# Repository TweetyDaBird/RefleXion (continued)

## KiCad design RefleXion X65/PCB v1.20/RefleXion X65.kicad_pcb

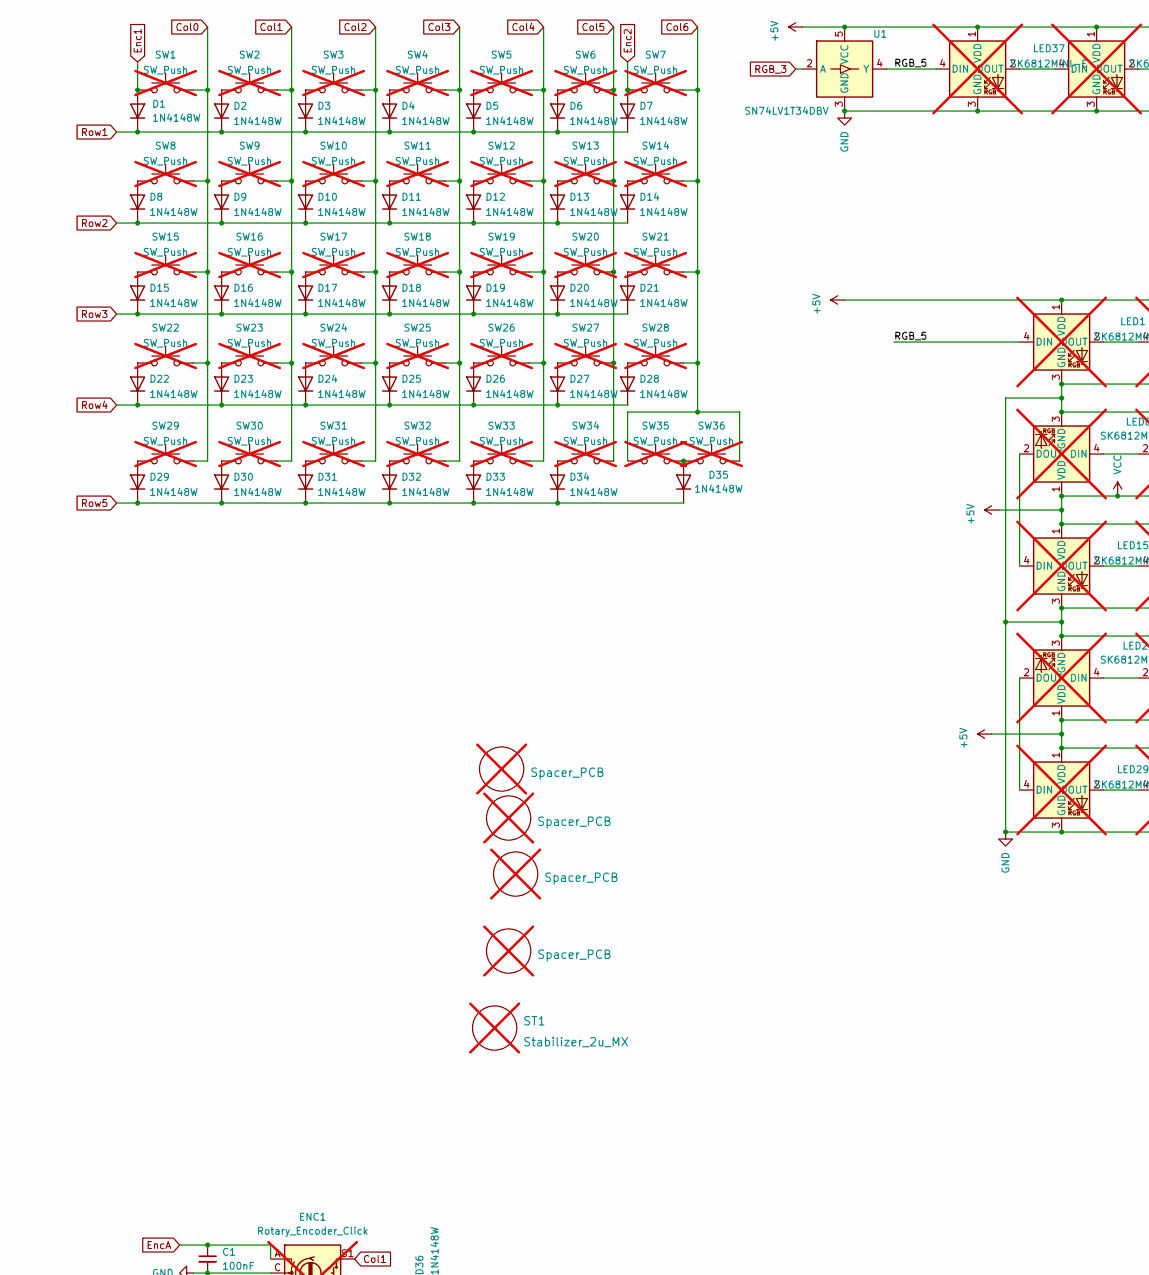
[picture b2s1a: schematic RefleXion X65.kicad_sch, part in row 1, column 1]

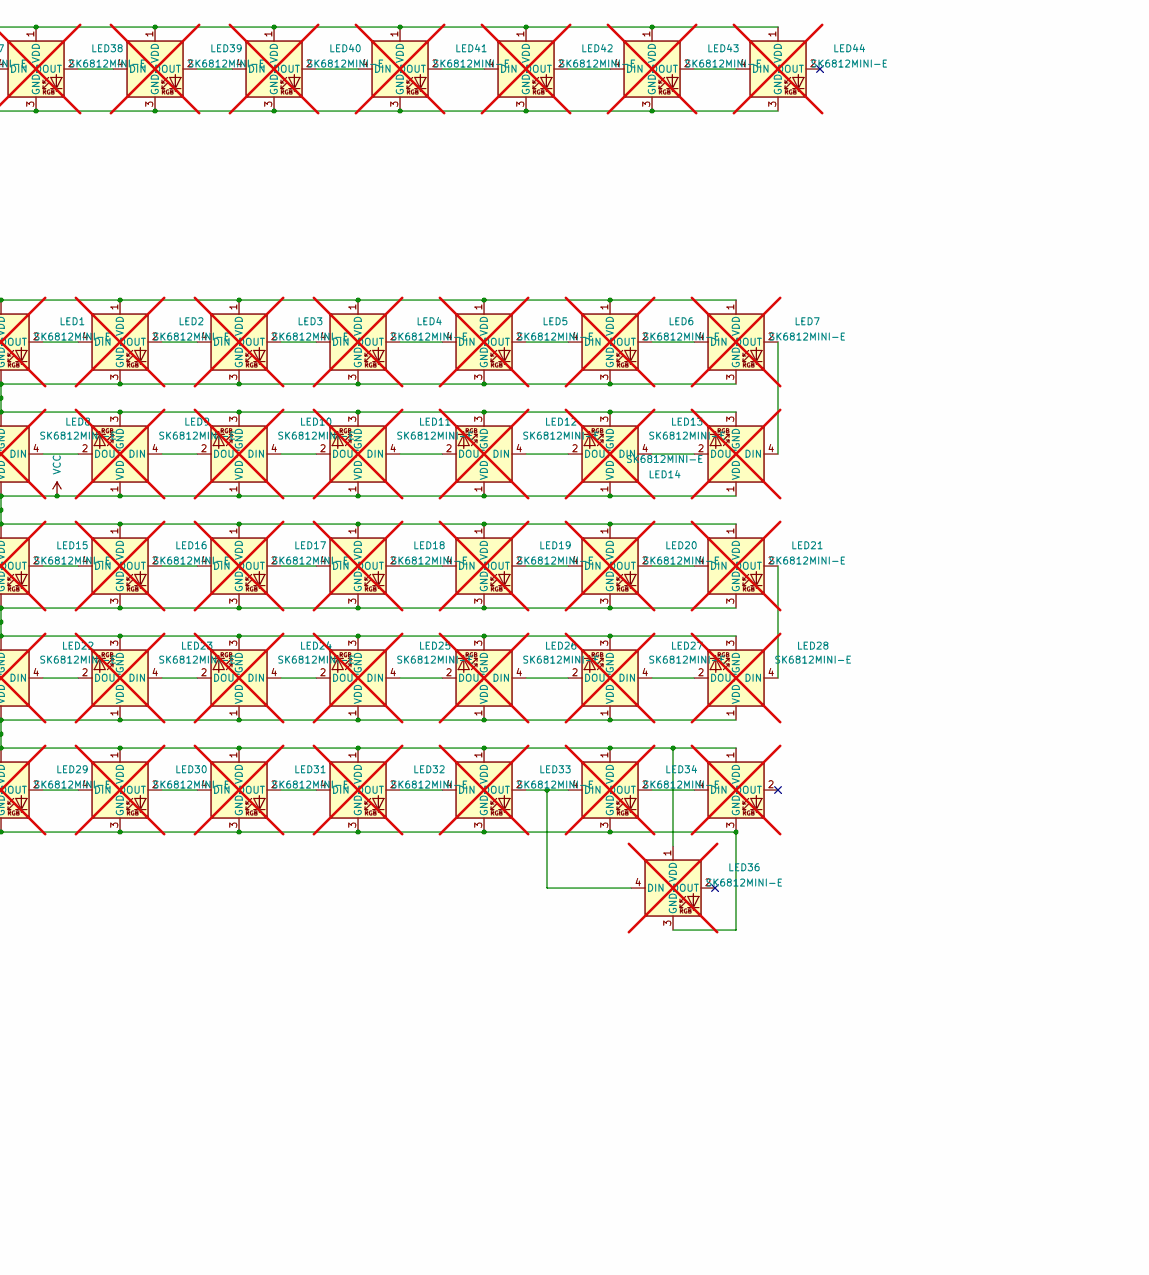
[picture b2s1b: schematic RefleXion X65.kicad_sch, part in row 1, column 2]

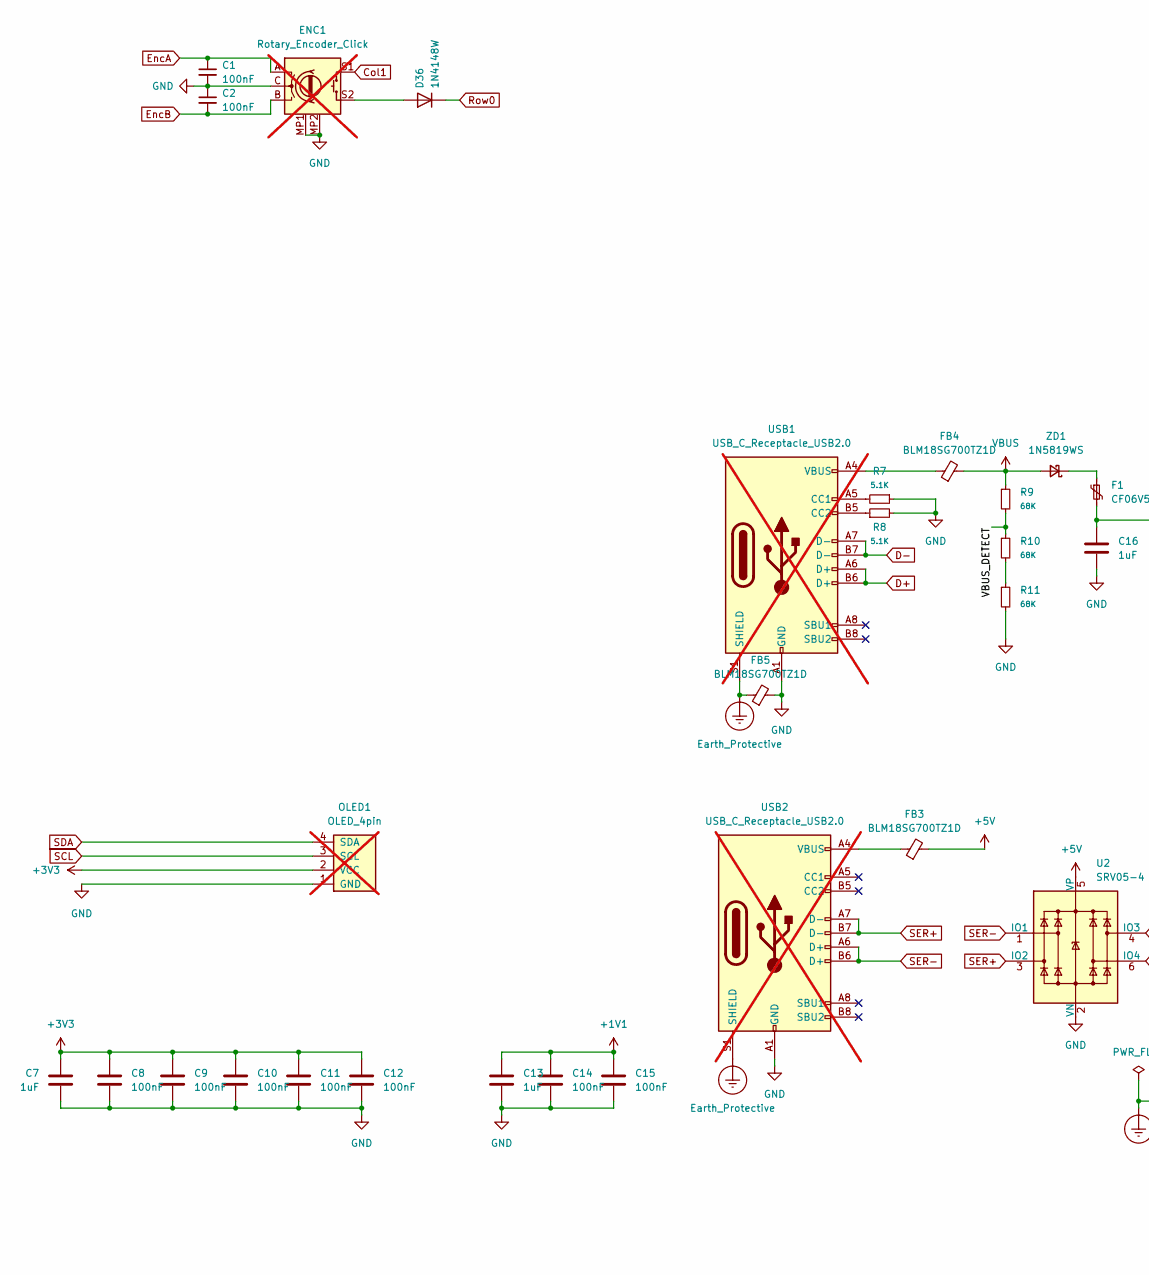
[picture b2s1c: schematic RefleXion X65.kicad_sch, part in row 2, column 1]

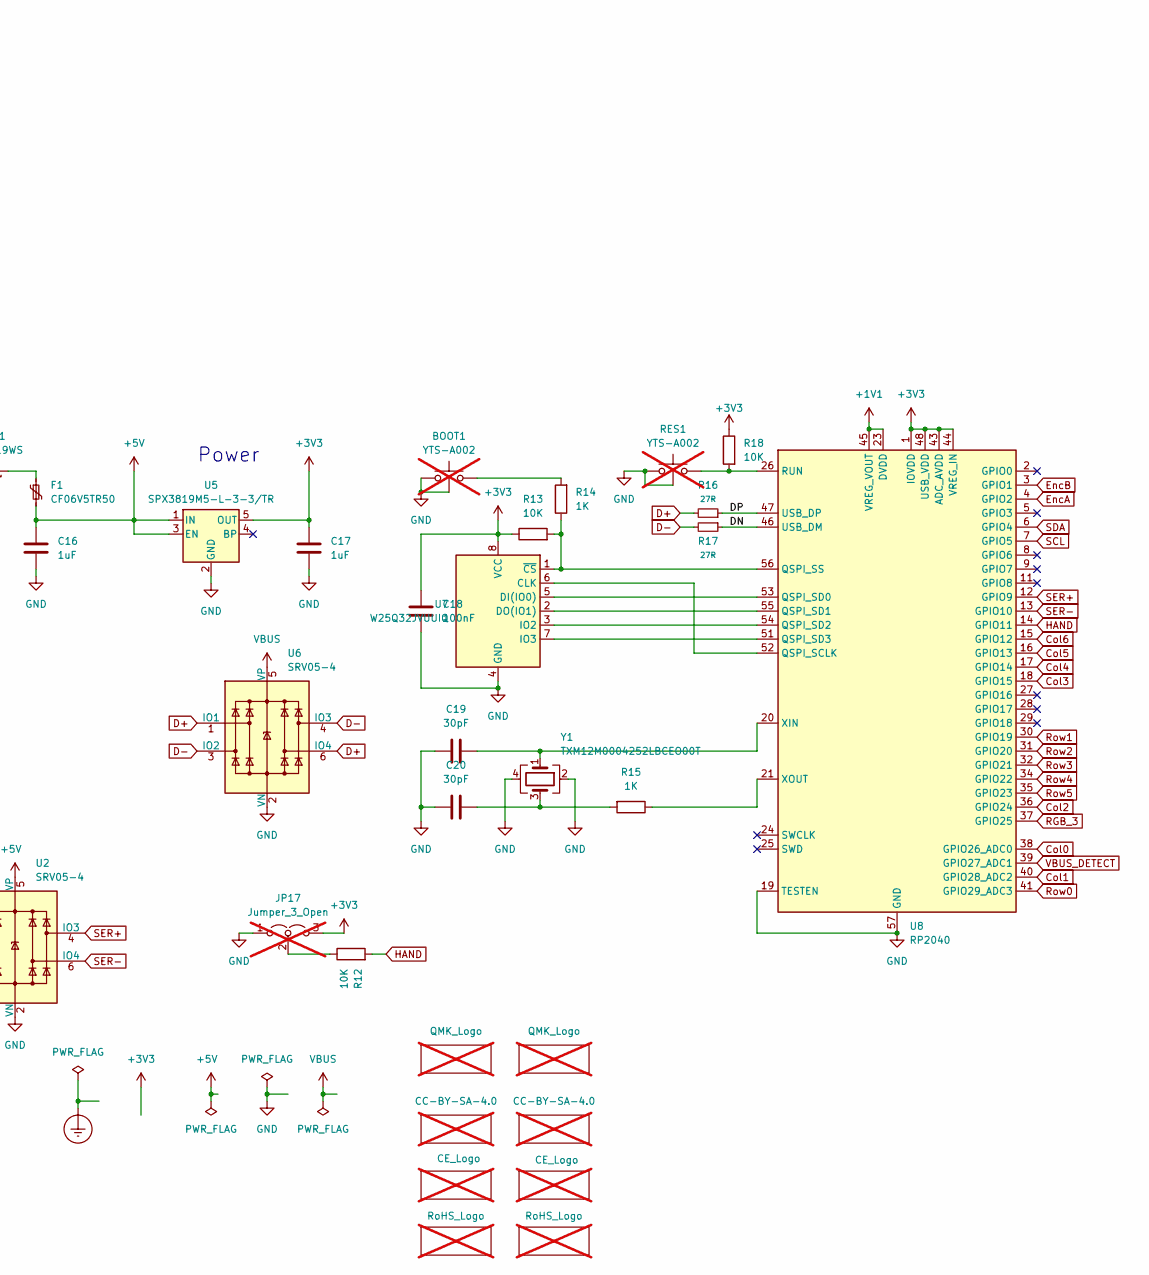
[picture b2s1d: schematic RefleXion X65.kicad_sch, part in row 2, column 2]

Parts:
BOOT1: YTS-A002; LCSC C2910650; not fitted
C1, C2, C8, C9, C10, C11, C12, C14, C15, C18: 100nF; C_0402_1005Metric; LCSC C1525
C7, C13, C16, C17: 1uF; C_0402_1005Metric; LCSC C52923
C19, C20: 30pF; C_0402_1005Metric; LCSC C1570
D1, D2, D3, D4, D5, D6, D7, D8, D9, D10, D11, D12, D13, D14, D15, D16, D17, D18, D19, D20, D21, D22, D23, D24, D25, D26, D27, D28, D29, D30, D31, D32, D33, D34, D35, D36: 1N4148W; D_SOD-123; LCSC C81598
ENC1: Rotary_Encoder_Click; Encoder_Alps_EC11E_Small; not fitted
F1: CF06V5TR50; R_0603_1608Metric; LCSC C163116
FB3, FB4, FB5: BLM18SG700TZ1D; C_0603_1608Metric_Pad1.08x0.95mm_HandSolder; LCSC C1002
H1, H2, H3, H4: Spacer_PCB; Spacer PCB hole; not fitted
JP17: Jumper_3_Open; SolderJumper-3_open_mini; not fitted
LED1, LED2, LED3, LED4, LED5, LED6, LED7, LED8, LED9, LED10, LED11, LED12, LED13, LED14, LED15, LED16, LED17, LED18, LED19, LED20, LED21, LED22, LED23, LED24, LED25, LED26, LED27, LED28, LED29, LED30, LED31, LED32, LED33: SK6812MINI-E; MX_SK6812MINI-E_REVERSIBLE; not fitted
LED34, LED35, LED36, LED37, LED38, LED39, LED40, LED41, LED42, LED43, LED44: SK6812MINI-E; MX_SK6812MINI-E_REVERSIBLE_special; not fitted
Logo1, Logo2: CE_Logo; CE; not fitted
Logo3, Logo6: CC-BY-SA-4.0; CC_BY_SA_40; not fitted
Logo4, Logo5: QMK_Logo; RoHS; not fitted
Logo7, Logo8: RoHS_Logo; RoHs; not fitted
OLED1: OLED_4pin; SSD1306-0.91-OLED-4pin-128x32 doublesided; not fitted
R7, R8: 5.1K; R_0402_1005Metric; LCSC C25905
R9, R10, R11: 68K; R_0402_1005Metric; LCSC C137947
R12, R13, R18: 10K; R_0402_1005Metric; LCSC C25744
R14, R15: 1K; R_0402_1005Metric; LCSC C11702
R16, R17: 27R; R_0402_1005Metric; LCSC C321419
RES1: YTS-A002; LCSC C2910650; not fitted
ST1: Stabilizer_2u_MX; Stabilizer_Cherry_MX_2.00u; not fitted
SW1, SW2, SW3, SW4, SW5, SW6, SW7, SW8, SW9, SW10, SW11, SW12, SW13, SW14, SW15, SW16, SW17, SW18, SW19, SW20, SW21, SW22, SW23, SW24, SW25, SW26, SW27, SW28, SW29, SW30, SW31, SW32, SW33, SW34, SW35, SW36: SW_Push; SW_MX_HotSwap_Reversible; not fitted
U1: SN74LV1T34DBV; SOT-23-5; LCSC C100024
U2, U6: SRV05-4; SOT-23-6; LCSC C7420376
U5: SPX3819M5-L-3-3/TR; SOT-23-5; LCSC C9055
U7: W25Q32JVUUIQ; USON-8_4x3mm_P0.8mm; LCSC C2999380
U8: RP2040; QFN-56-1EP_7x7mm_P0.4mm_EP3.2x3.2mm_ThermalVias; LCSC C2040
USB1, USB2: USB_C_Receptacle_USB2.0; Molex-216990_GCT-USB45xx_HRO-TYPE-C-31-M-13x-PiMicro; LCSC C963373; not fitted
Y1: TXM12M0004252LBCEO00T; Crystal_SMD_2520-4Pin_2.5x2.0mm; LCSC C284156
ZD1: 1N5819WS; D_SOD-323F; LCSC C191023

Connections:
+1V1: C13.1, C14.1, C15.1, U8.23 (DVDD), U8.45 (VREG_VOUT), U8.50 (DVDD)
+3V3: C7.1, C8.1, C9.1, C10.1, C11.1, C12.1, C17.1, C18.1, JP17.3 (B), OLED1.2 (VCC), R13.1, R18.1, U5.5 (OUT), U7.8 (VCC), U8.1 (IOVDD), U8.10 (IOVDD), U8.22 (IOVDD), U8.33 (IOVDD), U8.42 (IOVDD), U8.43 (ADC_AVDD), U8.44 (VREG_IN), U8.48 (USB_VDD), U8.49 (IOVDD)
+5V: C16.1, F1.2, FB3.2, LED1.1 (VDD), LED2.1 (VDD), LED3.1 (VDD), LED4.1 (VDD), LED5.1 (VDD), LED6.1 (VDD), LED7.1 (VDD), LED8.1 (VDD), LED9.1 (VDD), LED10.1 (VDD), LED11.1 (VDD), LED12.1 (VDD), LED13.1 (VDD), LED14.1 (VDD), LED15.1 (VDD), LED16.1 (VDD), LED17.1 (VDD), LED18.1 (VDD), LED19.1 (VDD), LED20.1 (VDD), LED21.1 (VDD), LED22.1 (VDD), LED23.1 (VDD), LED24.1 (VDD), LED25.1 (VDD), LED26.1 (VDD), LED27.1 (VDD), LED28.1 (VDD), LED29.1 (VDD), LED30.1 (VDD), LED31.1 (VDD), LED32.1 (VDD), LED33.1 (VDD), LED34.1 (VDD), LED35.1 (VDD), LED36.1 (VDD), LED37.1 (VDD), LED38.1 (VDD), LED39.1 (VDD), LED40.1 (VDD), LED41.1 (VDD), LED42.1 (VDD), LED43.1 (VDD), LED44.1 (VDD), U1.5 (VCC), U2.5 (VP), U5.1 (IN), U5.3 (EN)
/DN: R17.1, U8.46 (USB_DM)
/DP: R16.1, U8.47 (USB_DP)
/RGB_5: LED1.4 (DIN), LED37.4 (DIN), U1.4 (Y)
Col0: SW1.1, SW8.1, SW15.1, SW22.1, SW29.1, U8.38 (GPIO26_ADC0)
Col1: ENC1.S1, SW2.2, SW9.2, SW16.2, SW23.2, SW30.2, U8.40 (GPIO28_ADC2)
Col2: SW3.2, SW10.2, SW17.2, SW24.2, SW31.2, U8.36 (GPIO24)
Col3: SW4.2, SW11.2, SW18.2, SW25.2, SW32.2, U8.18 (GPIO15)
Col4: SW5.2, SW12.2, SW19.2, SW26.2, SW33.2, U8.17 (GPIO14)
Col5: SW6.2, SW13.2, SW20.2, SW27.2, SW34.2, U8.16 (GPIO13)
Col6: SW7.2, SW14.2, SW21.2, SW28.2, SW35.1, SW36.2, U8.15 (GPIO12)
D+: R16.2, U6.1 (IO1), U6.6 (IO4), USB1.A6 (D+), USB1.B6 (D+)
D-: R17.2, U6.3 (IO2), U6.4 (IO3), USB1.A7 (D-), USB1.B7 (D-)
Earth_Protective: FB5.1, USB1.S1 (SHIELD), USB2.S1 (SHIELD)
Enc1: D1.2 (A), SW1.2
Enc2: D7.2 (A), SW7.1
EncA: C1.1, ENC1.A, U8.4 (GPIO2)
EncB: C2.2, ENC1.B, U8.3 (GPIO1)
GND: BOOT1.2, BOOT1.3, C1.2, C2.1, C7.2, C8.2, C9.2, C10.2, C11.2, C12.2, C13.2, C14.2, C15.2, C16.2, C17.2, C18.2, C19.2, C20.2, ENC1.C, ENC1.MP1 (GND), ENC1.MP2 (GND), FB5.2, JP17.1 (A), LED1.3 (GND), LED2.3 (GND), LED3.3 (GND), LED4.3 (GND), LED5.3 (GND), LED6.3 (GND), LED7.3 (GND), LED8.3 (GND), LED9.3 (GND), LED10.3 (GND), LED11.3 (GND), LED12.3 (GND), LED13.3 (GND), LED14.3 (GND), LED15.3 (GND), LED16.3 (GND), LED17.3 (GND), LED18.3 (GND), LED19.3 (GND), LED20.3 (GND), LED21.3 (GND), LED22.3 (GND), LED23.3 (GND), LED24.3 (GND), LED25.3 (GND), LED26.3 (GND), LED27.3 (GND), LED28.3 (GND), LED29.3 (GND), LED30.3 (GND), LED31.3 (GND), LED32.3 (GND), LED33.3 (GND), LED34.3 (GND), LED35.3 (GND), LED36.3 (GND), LED37.3 (GND), LED38.3 (GND), LED39.3 (GND), LED40.3 (GND), LED41.3 (GND), LED42.3 (GND), LED43.3 (GND), LED44.3 (GND), OLED1.1 (GND), R7.1, R8.2, R11.2, RES1.2, RES1.3, U1.3 (GND), U2.2 (VN), U5.2 (GND), U6.2 (VN), U7.4 (GND), U8.19 (TESTEN), U8.57 (GND), USB1.A1 (GND), USB1.A12 (GND), USB1.B1 (GND), USB1.B12 (GND), USB2.A1 (GND), USB2.A12 (GND), USB2.B1 (GND), USB2.B12 (GND), Y1.2, Y1.4
HAND: R12.2, U8.14 (GPIO11)
unnamed: BOOT1.1, R14.2
unnamed: C20.1, R15.2, Y1.3
unnamed: D2.2 (A), SW2.1
unnamed: D3.2 (A), SW3.1
unnamed: D4.2 (A), SW4.1
unnamed: D5.2 (A), SW5.1
unnamed: D6.2 (A), SW6.1
unnamed: D8.2 (A), SW8.2
unnamed: D9.2 (A), SW9.1
unnamed: D10.2 (A), SW10.1
unnamed: D11.2 (A), SW11.1
unnamed: D12.2 (A), SW12.1
unnamed: D13.2 (A), SW13.1
unnamed: D14.2 (A), SW14.1
unnamed: D15.2 (A), SW15.2
unnamed: D16.2 (A), SW16.1
unnamed: D17.2 (A), SW17.1
unnamed: D18.2 (A), SW18.1
unnamed: D19.2 (A), SW19.1
unnamed: D20.2 (A), SW20.1
unnamed: D21.2 (A), SW21.1
unnamed: D22.2 (A), SW22.2
unnamed: D23.2 (A), SW23.1
unnamed: D24.2 (A), SW24.1
unnamed: D25.2 (A), SW25.1
unnamed: D26.2 (A), SW26.1
unnamed: D27.2 (A), SW27.1
unnamed: D28.2 (A), SW28.1
unnamed: D29.2 (A), SW29.2
unnamed: D30.2 (A), SW30.1
unnamed: D31.2 (A), SW31.1
unnamed: D32.2 (A), SW32.1
unnamed: D33.2 (A), SW33.1
unnamed: D34.2 (A), SW34.1
unnamed: D35.2 (A), SW35.2, SW36.1
unnamed: D36.2 (A), ENC1.S2
unnamed: FB3.1, USB2.A4 (VBUS), USB2.A9 (VBUS), USB2.B4 (VBUS), USB2.B9 (VBUS)
unnamed: FB4.1, USB1.A4 (VBUS), USB1.A9 (VBUS), USB1.B4 (VBUS), USB1.B9 (VBUS)
unnamed: JP17.2 (C), R12.1
unnamed: LED1.2 (DOUT), LED2.4 (DIN)
unnamed: LED2.2 (DOUT), LED3.4 (DIN)
unnamed: LED3.2 (DOUT), LED4.4 (DIN)
unnamed: LED4.2 (DOUT), LED5.4 (DIN)
unnamed: LED5.2 (DOUT), LED6.4 (DIN)
unnamed: LED6.2 (DOUT), LED7.4 (DIN)
unnamed: LED8.4 (DIN), LED9.2 (DOUT)
unnamed: LED10.4 (DIN), LED11.2 (DOUT)
unnamed: LED9.4 (DIN), LED10.2 (DOUT)
unnamed: LED11.4 (DIN), LED12.2 (DOUT)
unnamed: LED12.4 (DIN), LED13.2 (DOUT)
unnamed: LED13.4 (DIN), LED14.2 (DOUT)
unnamed: LED7.2 (DOUT), LED14.4 (DIN)
unnamed: LED8.2 (DOUT), LED15.4 (DIN)
unnamed: LED15.2 (DOUT), LED16.4 (DIN)
unnamed: LED16.2 (DOUT), LED17.4 (DIN)
unnamed: LED17.2 (DOUT), LED18.4 (DIN)
unnamed: LED18.2 (DOUT), LED19.4 (DIN)
unnamed: LED19.2 (DOUT), LED20.4 (DIN)
unnamed: LED20.2 (DOUT), LED21.4 (DIN)
unnamed: LED21.2 (DOUT), LED28.4 (DIN)
unnamed: LED22.4 (DIN), LED23.2 (DOUT)
unnamed: LED22.2 (DOUT), LED29.4 (DIN)
unnamed: LED23.4 (DIN), LED24.2 (DOUT)
unnamed: LED24.4 (DIN), LED25.2 (DOUT)
unnamed: LED25.4 (DIN), LED26.2 (DOUT)
unnamed: LED26.4 (DIN), LED27.2 (DOUT)
unnamed: LED27.4 (DIN), LED28.2 (DOUT)
unnamed: LED29.2 (DOUT), LED30.4 (DIN)
unnamed: LED30.2 (DOUT), LED31.4 (DIN)
unnamed: LED31.2 (DOUT), LED32.4 (DIN)
unnamed: LED32.2 (DOUT), LED33.4 (DIN)
unnamed: LED33.2 (DOUT), LED34.4 (DIN), LED36.4 (DIN)
unnamed: LED34.2 (DOUT), LED35.4 (DIN)
unnamed: LED37.2 (DOUT), LED38.4 (DIN)
unnamed: LED38.2 (DOUT), LED39.4 (DIN)
unnamed: LED39.2 (DOUT), LED40.4 (DIN)
unnamed: LED40.2 (DOUT), LED41.4 (DIN)
unnamed: LED41.2 (DOUT), LED42.4 (DIN)
unnamed: LED42.2 (DOUT), LED43.4 (DIN)
unnamed: LED43.2 (DOUT), LED44.4 (DIN)
unnamed: R10.2, R11.1
unnamed: U7.6 (CLK), U8.52 (QSPI_SCLK)
unnamed: U7.5 (DI(IO0)), U8.53 (QSPI_SD0)
unnamed: U7.2 (DO(IO1)), U8.55 (QSPI_SD1)
unnamed: U7.3 (IO2), U8.54 (QSPI_SD2)
unnamed: U7.7 (IO3), U8.51 (QSPI_SD3)
unnamed: R13.2, R14.1, U7.1 (~CS), U8.56 (QSPI_SS)
unnamed: R18.2, RES1.1, U8.26 (RUN)
unnamed: C19.1, U8.20 (XIN), Y1.1
unnamed: R15.1, U8.21 (XOUT)
unnamed: R7.2, USB1.A5 (CC1)
unnamed: R8.1, USB1.B5 (CC2)
unnamed: F1.1, ZD1.1 (K)
RGB_3: U1.2 (A), U8.37 (GPIO25)
Row0: D36.1 (K), U8.41 (GPIO29_ADC3)
Row1: D1.1 (K), D2.1 (K), D3.1 (K), D4.1 (K), D5.1 (K), D6.1 (K), D7.1 (K), U8.30 (GPIO19)
Row2: D8.1 (K), D9.1 (K), D10.1 (K), D11.1 (K), D12.1 (K), D13.1 (K), D14.1 (K), U8.31 (GPIO20)
Row3: D15.1 (K), D16.1 (K), D17.1 (K), D18.1 (K), D19.1 (K), D20.1 (K), D21.1 (K), U8.32 (GPIO21)
Row4: D22.1 (K), D23.1 (K), D24.1 (K), D25.1 (K), D26.1 (K), D27.1 (K), D28.1 (K), U8.34 (GPIO22)
Row5: D29.1 (K), D30.1 (K), D31.1 (K), D32.1 (K), D33.1 (K), D34.1 (K), D35.1 (K), U8.35 (GPIO23)
SCL: OLED1.3 (SCL), U8.7 (GPIO5)
SDA: OLED1.4 (SDA), U8.6 (GPIO4)
SER+: U2.3 (IO2), U2.4 (IO3), U8.12 (GPIO9), USB2.A7 (D-), USB2.B7 (D-)
SER-: U2.1 (IO1), U2.6 (IO4), U8.13 (GPIO10), USB2.A6 (D+), USB2.B6 (D+)
VBUS: FB4.2, R9.1, U6.5 (VP), ZD1.2 (A)
VBUS_DETECT: R9.2, R10.1, U8.39 (GPIO27_ADC1)

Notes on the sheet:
Power

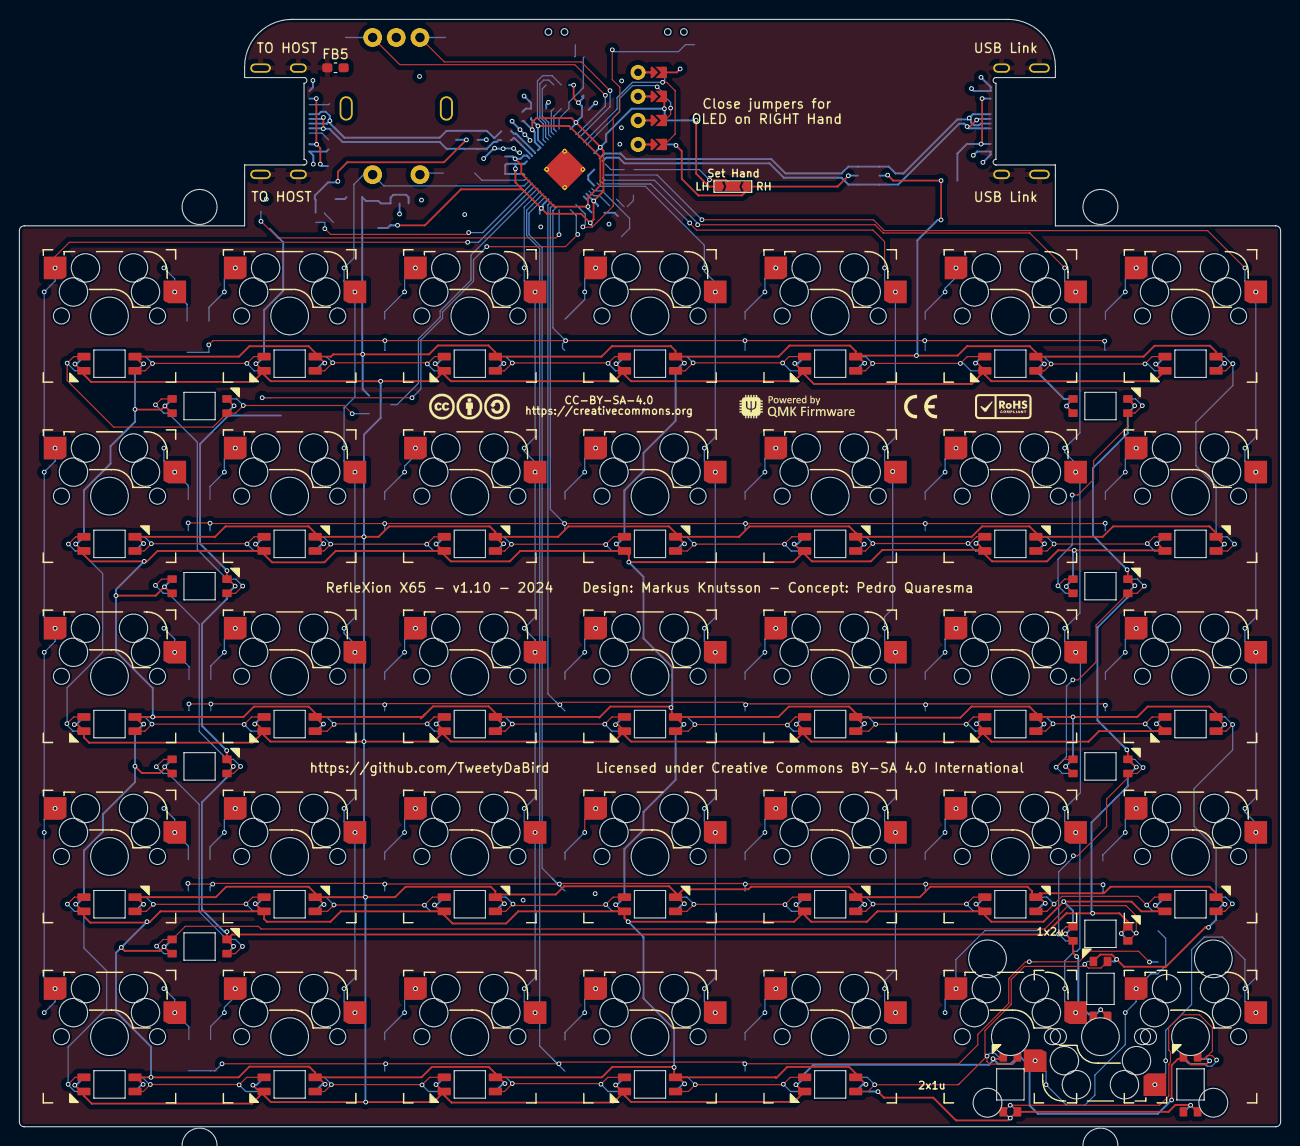
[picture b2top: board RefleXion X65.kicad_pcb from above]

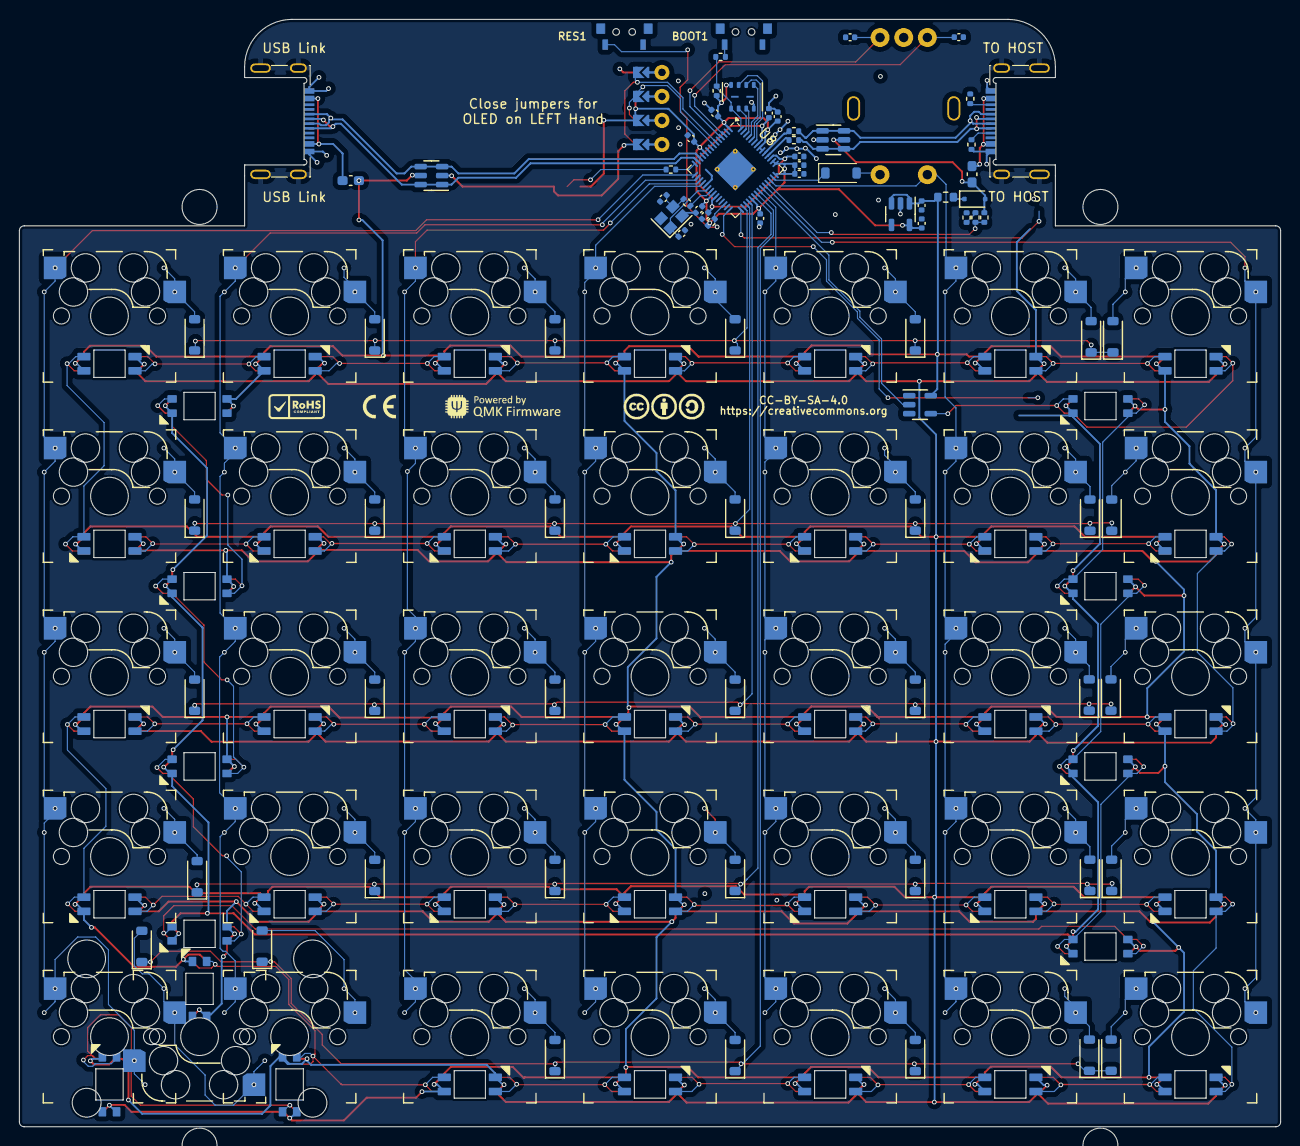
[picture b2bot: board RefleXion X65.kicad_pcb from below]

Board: 2 copper layers, 133.4 x 117.1 mm, 176 parts (83 on the bottom side), 128 nets.

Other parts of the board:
Logo4#2: QMK_Logo; Powered_by_QMK

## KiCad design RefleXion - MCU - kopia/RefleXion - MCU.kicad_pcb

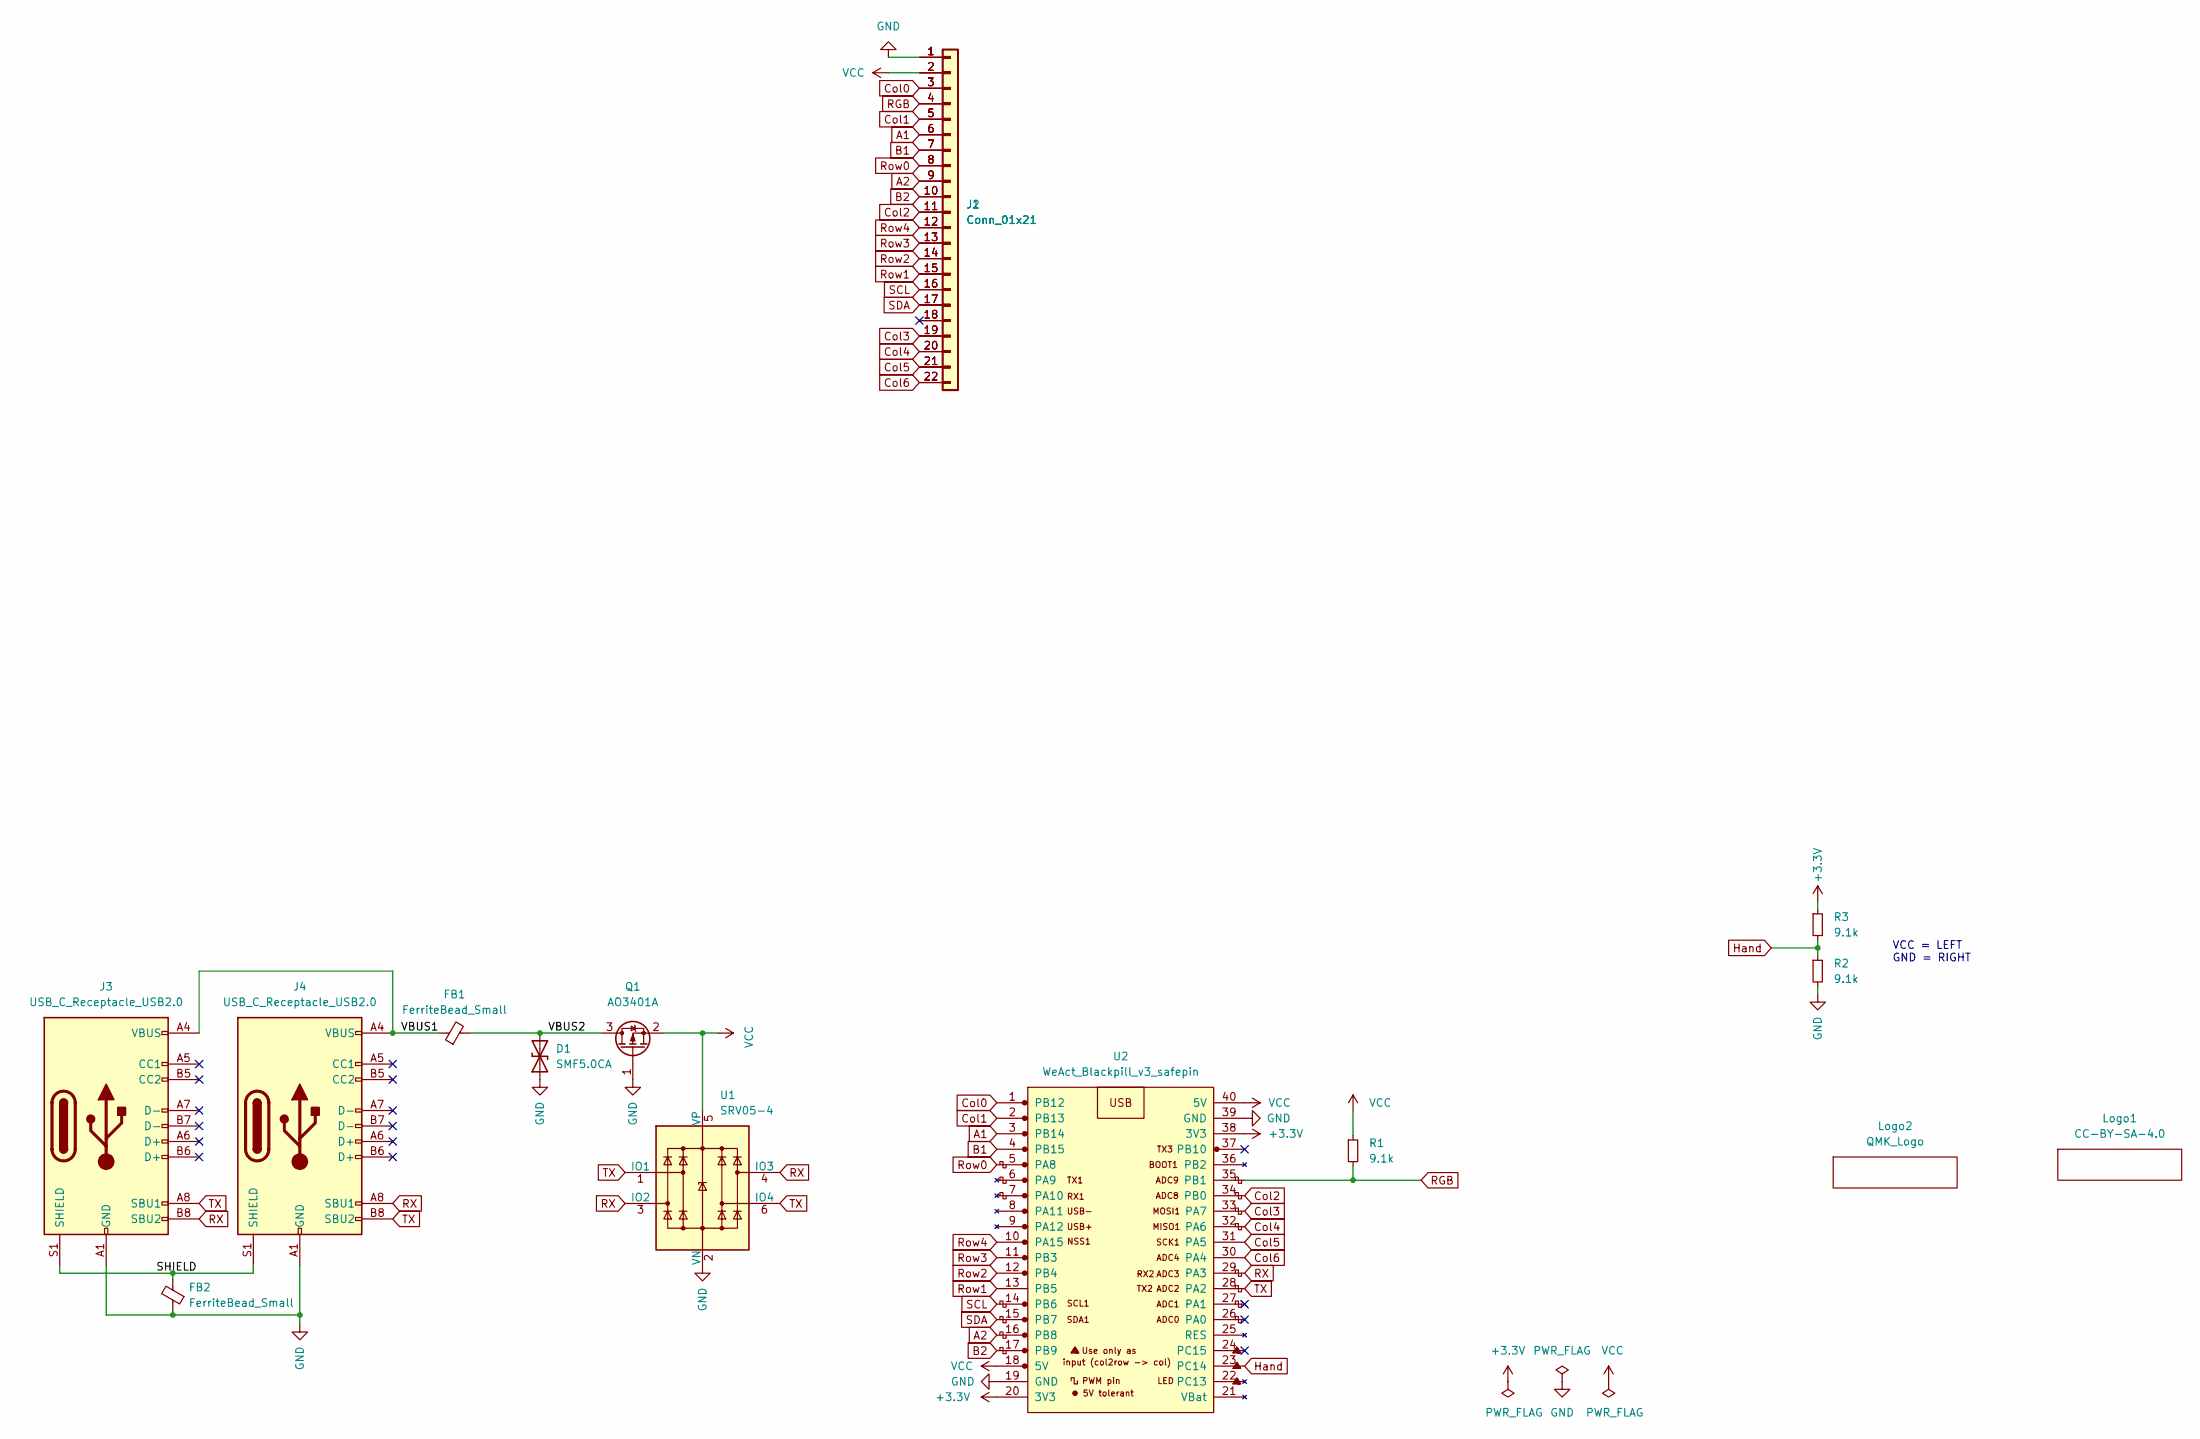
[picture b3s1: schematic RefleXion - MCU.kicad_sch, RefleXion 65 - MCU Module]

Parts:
D1: SMF5.0CA; D_SOD-123
FB1, FB2: FerriteBead_Small; C_0805_2012Metric_Pad1.18x1.45mm_HandSolder
J1, J2: Conn_01x21; PinHeader_1x22_P2.54mm_Vertical
J3, J4: USB_C_Receptacle_USB2.0; HRO_TYPE-C-31-M-12
Logo1: CC-BY-SA-4.0; CC_BY_SA_40
Logo2: QMK_Logo; Powered_by_QMK
Q1: AO3401A; SOT-23
R1, R2, R3: 9.1k; R_0603_1608Metric_Pad0.98x0.95mm_HandSolder
U1: SRV05-4; SOT-23-6_Handsoldering
U2: WeAct_Blackpill_v3_safepin; WeAct_BlackPill_3_reverse_mount

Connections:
+3.3V: R3.1, U2.20 (3V3), U2.38 (3V3)
/SHIELD: FB2.2, J3.S1 (SHIELD), J4.S1 (SHIELD)
/VBUS1: FB1.1, J3.A4 (VBUS), J3.A9 (VBUS), J3.B4 (VBUS), J3.B9 (VBUS), J4.A4 (VBUS), J4.A9 (VBUS), J4.B4 (VBUS), J4.B9 (VBUS)
/VBUS2: D1.2 (A2), FB1.2, Q1.3 (D)
A1: J1.6, J2.6, U2.3 (PB14)
A2: J1.9, J2.9, U2.16 (PB8)
B1: J1.7, J2.7, U2.4 (PB15)
B2: J1.10, J2.10, U2.17 (PB9)
Col0: J1.3, J2.3, U2.1 (PB12)
Col1: J1.5, J2.5, U2.2 (PB13)
Col2: J1.11, J2.11, U2.34 (PB0)
Col3: J1.19, J2.19, U2.33 (PA7)
Col4: J1.20, J2.20, U2.32 (PA6)
Col5: J1.21, J2.21, U2.31 (PA5)
Col6: J1.22, J2.22, U2.30 (PA4)
GND: D1.1 (A1), FB2.1, J1.1, J2.1, J3.A1 (GND), J3.A12 (GND), J3.B1 (GND), J3.B12 (GND), J4.A1 (GND), J4.A12 (GND), J4.B1 (GND), J4.B12 (GND), Q1.1 (G), R2.2, U1.2 (VN), U2.19 (GND), U2.39 (GND)
Hand: R2.1, R3.2, U2.23 (PC14)
RGB: J1.4, J2.4, R1.2, U2.35 (PB1)
RX: J3.B8 (SBU2), J4.A8 (SBU1), U1.3 (IO2), U1.4 (IO3), U2.29 (PA3)
Row0: J1.8, J2.8, U2.5 (PA8)
Row1: J1.15, J2.15, U2.13 (PB5)
Row2: J1.14, J2.14, U2.12 (PB4)
Row3: J1.13, J2.13, U2.11 (PB3)
Row4: J1.12, J2.12, U2.10 (PA15)
SCL: J1.16, J2.16, U2.14 (PB6)
SDA: J1.17, J2.17, U2.15 (PB7)
TX: J3.A8 (SBU1), J4.B8 (SBU2), U1.1 (IO1), U1.6 (IO4), U2.28 (PA2)
VCC: J1.2, J2.2, Q1.2 (S), R1.1, U1.5 (VP), U2.18 (5V), U2.40 (5V)

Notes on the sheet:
VCC = LEFT GND = RIGHT

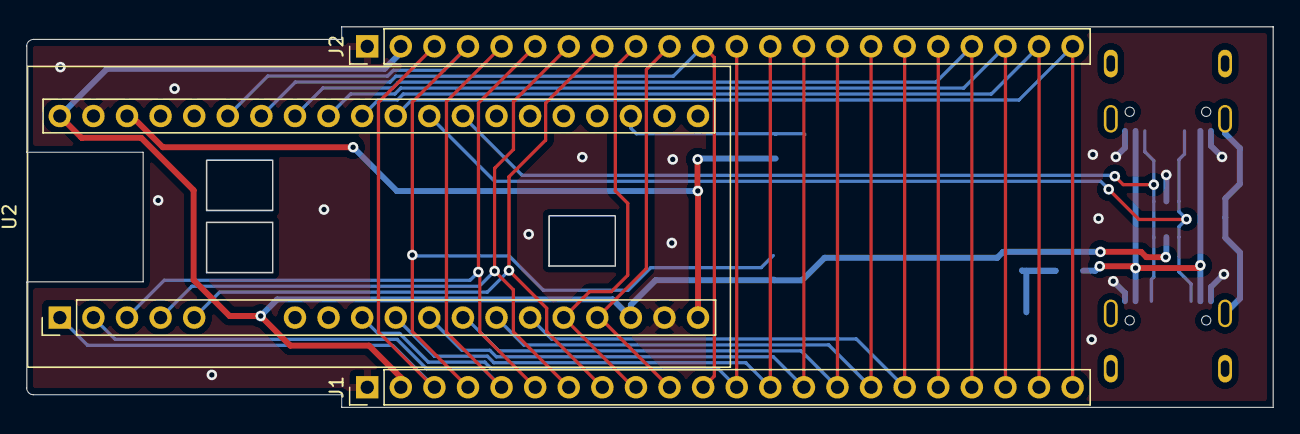
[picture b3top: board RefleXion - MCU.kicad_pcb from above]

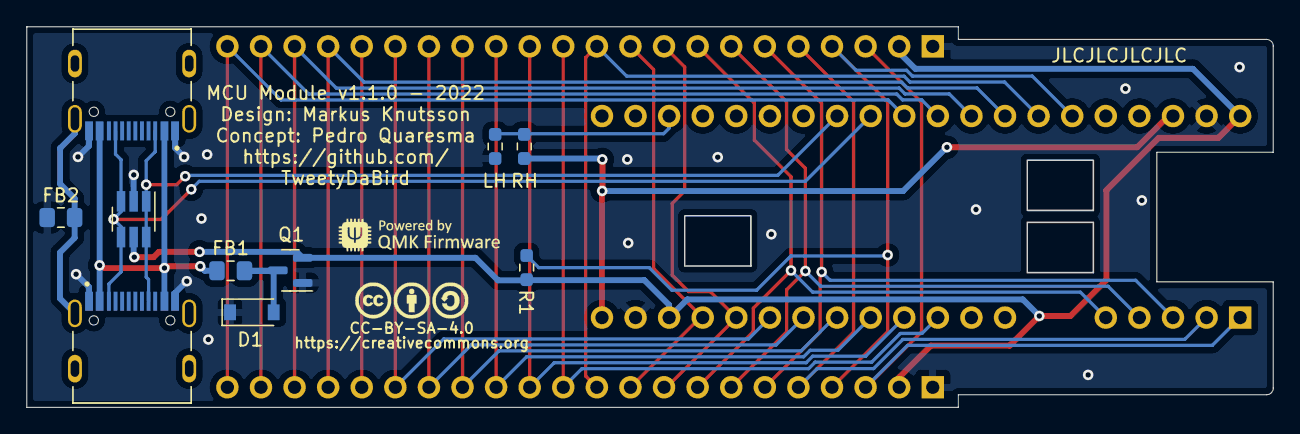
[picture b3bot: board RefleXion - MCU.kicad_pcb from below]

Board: 2 copper layers, 94.3 x 28.8 mm, 15 parts (12 on the bottom side), 28 nets.
